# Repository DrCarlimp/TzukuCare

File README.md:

# README - TZUKU Care

## Descripción del Proyecto

**TZUKU Care** es un sistema de monitoreo complementario para perros de asistencia, diseñado para mejorar la calidad de vida de personas con condiciones que dificultan llevar una vida plena. Este sistema combina la capacidad sensorial de los perros de asistencia con tecnologías avanzadas de monitoreo y análisis de sonido, ofreciendo una solución no invasiva basada en computación en el borde.

### Características principales:
- **Detección de patrones de ladridos:** Identifica ladridos específicos de perros entrenados para activar alarmas.
- **Privacidad y comodidad:** Diseñado para no interferir con los usuarios o los perros.
- **Procesamiento local:** Elimina la dependencia de una conexión a Internet.
- **Aplicación personalizable:** Permite configurar las notificaciones y el monitoreo de ubicación.

## Responsables

- **Equipo de Desarrollo:**
  - Carlos Alberto Aguilar Lazcano
  - Claudia Angélica Rivera Romero
  - Edwin Raúl Abrego Ulloa
  - Marco Adame
  - Humberto Pérez Espinosa

- **Instituciones Participantes:**
  - Centro de Investigación Científica y de Educación Superior de Ensenada, Unidad Académica Tepic (CICESE-UAT)
  - Instituto Nacional de Astrofísica, Óptica y Electrónica (INAOE)
  - Universidad Autónoma de Tlaxcala

- **Responsables Técnicos:**
  - Dr. Ismael Edrein Espinosa Curiel - [ecuriel@cicese.edu.mx](mailto:ecuriel@cicese.edu.mx)
  - Dr. Humberto Pérez Espinosa - [humbertop@inaoep.mx](mailto:humbertop@inaoep.mx)

- **Página web:** [https://tzuku.cicese.mx/](https://tzuku.cicese.mx/)

## Instalación y Configuración Inicial

### Requisitos previos:
- Tarjeta Nvidia Jetson Nano (2GB)
- Tarjeta microSD con mínimo 16GB
- Acceso a Internet para configuración inicial

### Pasos para Configurar:
1. **Preparación de la tarjeta microSD:**
   - Descarga el sistema operativo desde la página oficial de Nvidia.
   - Usa `Etcher` para grabar la imagen en la tarjeta microSD.
   - Inserta la tarjeta en la Jetson Nano y realiza la configuración inicial.

2. **Preparación del modelo YAMNet:**
   - Descarga el modelo desde TensorFlow Hub.
   - Instala las dependencias necesarias usando `pip install`.

3. **Configuración del Firmware:**
   - Carga los scripts en Python para la gestión de datos y la comunicación entre componentes.
   - Configura los dispositivos como Arduino Nano y la pantalla LCD Nokia 5110 según el esquema provisto.

### Ejecución del Sistema
- **Modo Básico:** Ejecuta el script `alarmaExp.py` desde la terminal, configurando los parámetros necesarios.
- **Modo Avanzado:** Ejecuta el script `alarmaVF.py` para integración con API remota y monitoreo avanzado.

## Documentación

### Objetivos del Proyecto:
1. Implementar un sistema embebido para ejecutar modelos de machine learning localmente.
2. Diseñar un algoritmo que clasifique sonidos en tiempo real.
3. Evaluar el sistema en entornos controlados y reales.

### Diseño del Prototipo:
- Unidad de procesamiento: Nvidia Jetson Nano (2GB)
- Modelo de análisis: YAMNet
- Carcasa: Impresión 3D en PLA
- Componentes adicionales: Arduino Nano y pantalla LCD Nokia 5110

### Recursos Adicionales:
- **Scripts de Utilidades:**
  - `Alarm_plotter.ipynb`: Visualiza los eventos de activación.
  - `Alarms_events_detector.ipynb`: Simula configuraciones del algoritmo de detección.

## Contacto

Para consultas o soporte técnico, contacta a:
- **CICESE-UAT:** 311-129-5930, ext. 28607
- **INAOE:** 222-266-3100, ext. 8321

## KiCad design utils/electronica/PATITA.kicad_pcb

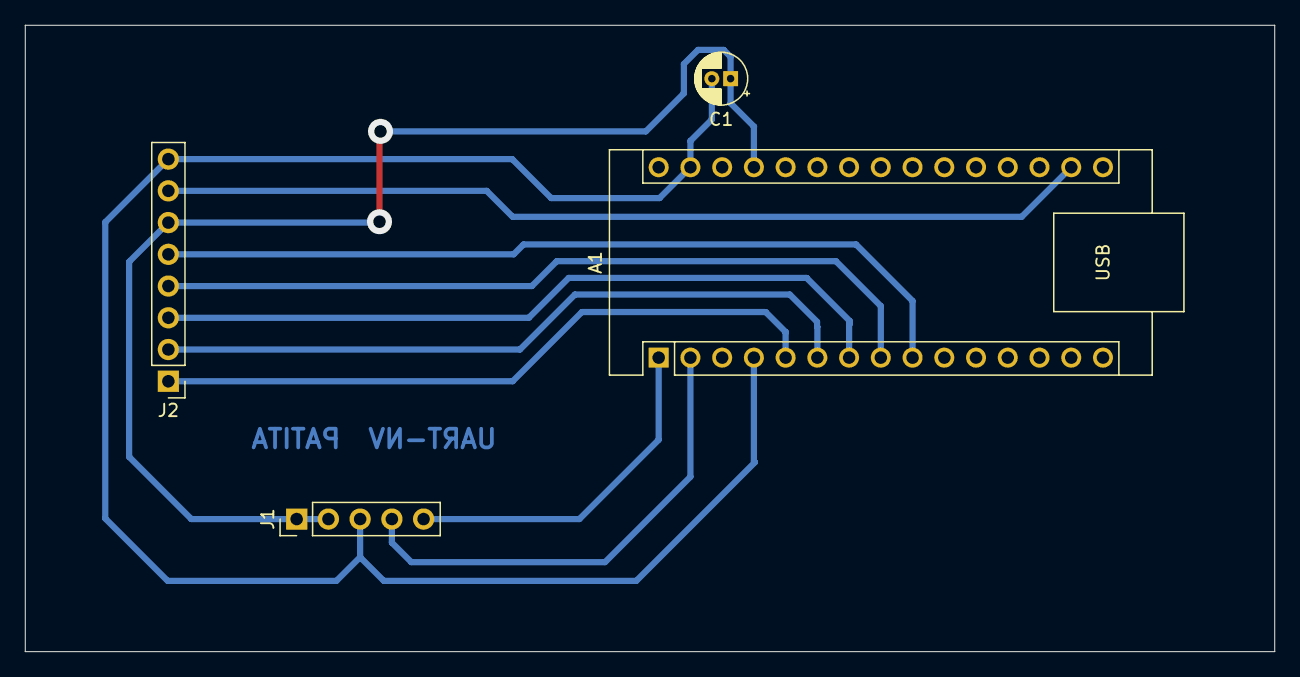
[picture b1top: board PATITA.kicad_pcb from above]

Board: 2 copper layers, 100.0 x 50.1 mm, 4 parts (0 on the bottom side), 10 nets.

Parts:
A1: Arduino_Nano_v2.x; Arduino_Nano
C1: C_Polarized; CP_Radial_D4.0mm_P1.50mm
J1: Jetson_Header; PinHeader_1x05_P2.54mm_Vertical
J2: Conn_01x08; PinHeader_1x08_P2.54mm_Vertical

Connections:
3.3V: A1.17 (3V3), J2.7
5V: A1.27 (+5V), C1.1, J1.1, J1.2, J2.6
D2: A1.5 (D2), J2.1
D3: A1.6 (D3), J2.2
D4: A1.7 (D4), J2.3
D5: A1.8 (D5), J2.4
D6: A1.9 (D6), J2.5
GND: A1.4 (GND), A1.29 (GND), C1.2, J1.3, J2.8
RX: A1.1 (D1/TX), J1.5
TX: A1.2 (D0/RX), J1.4

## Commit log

2024-12-24 añadiendo scripts y utilidades
2024-12-24 adding extra files
2024-12-24 acomodo de elementos
2024-12-24 acomodo de cosas
2024-12-24 añadido readme
